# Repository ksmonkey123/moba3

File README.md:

# moba3
 3rd generation moba control

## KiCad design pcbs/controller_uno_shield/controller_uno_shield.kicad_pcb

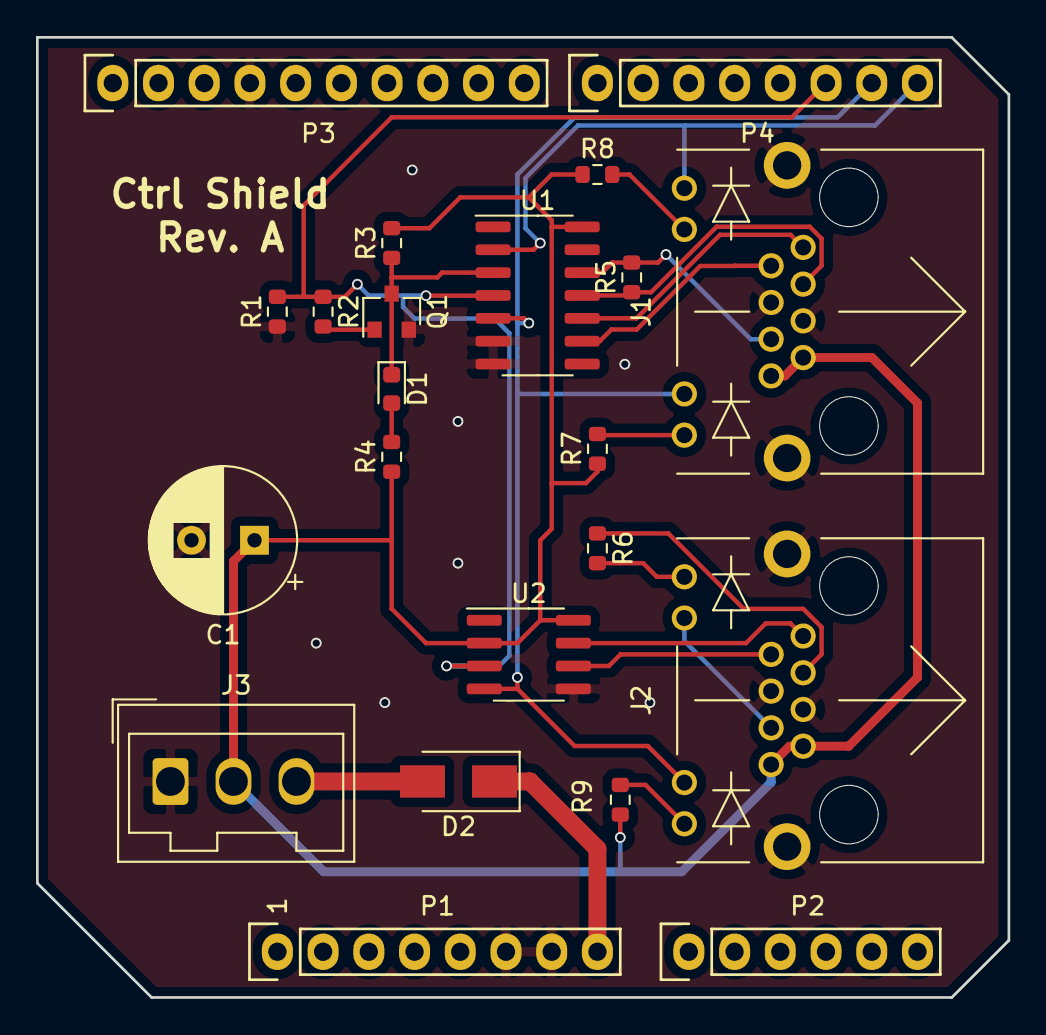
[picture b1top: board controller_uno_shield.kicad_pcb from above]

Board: 2 copper layers, 54.0 x 53.3 mm, 22 parts (0 on the bottom side), 24 nets.

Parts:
C1: CP; CP_Radial_D8.0mm_P3.50mm
D1: LED; LED_0603_1608Metric
D2: D_Schottky; D_SMA
J1, J2: RJ45_LED_Shielded; RND_RJ45_LED
J3: Screw_Terminal_01x03; Wago_734-133_1x03_P3.50mm_Vertical
P1: Power; Socket_Strip_Arduino_1x08
P2: Analog; Socket_Strip_Arduino_1x06
P3: Digital; Socket_Strip_Arduino_1x10
P4: Digital; Socket_Strip_Arduino_1x08
Q1: 2N7002; SOT-23
R1, R2, R3, R4: 10k; R_0603_1608Metric
R5: 2k; R_0603_1608Metric
R6, R7, R8, R9: 1k; R_0603_1608Metric
U1: MAX489E; SOIC-14_3.9x8.7mm_P1.27mm
U2: MAX481E; SOIC-8_3.9x4.9mm_P1.27mm

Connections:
5V: C1.1, J1.7, J1.8, J2.7, J2.8, J3.2, R3.2, R4.1, R7.1, R8.1, R9.1, U1.14, U2.2, U2.8
/0(Rx): J1.9, P4.8, U1.2
/1(Tx): J1.11, J2.11, P4.7, U1.5, U2.4
/2: P4.6, R1.2, R2.1, U1.4, U2.3
/A4(SDA): P2.5, P3.2
/A5(SCL): P2.6, P3.1
/Vin: D2.1, P1.8
/networking/~rx_en: D1.1, Q1.3, R3.1, U1.3
GND: C1.2, J1.4, J1.5, J1.SH, J2.4, J2.5, J2.SH, J3.1, P1.6, P1.7, P3.4, Q1.2, R1.1, U1.6, U1.7, U2.5
unnamed: D1.2, R4.2
unnamed: D2.2, J3.3
unnamed: J1.1, U1.10
unnamed: J1.2, U1.9
unnamed: J1.3, R5.1, U1.11
unnamed: J1.6, R5.2, U1.12
unnamed: J1.10, R8.2
unnamed: J1.12, R7.2
unnamed: J2.1, U2.7
unnamed: J2.2, U2.6
unnamed: J2.3, R6.1
unnamed: J2.9, R6.2
unnamed: J2.6, J2.10
unnamed: J2.12, R9.2
unnamed: Q1.1, R2.2

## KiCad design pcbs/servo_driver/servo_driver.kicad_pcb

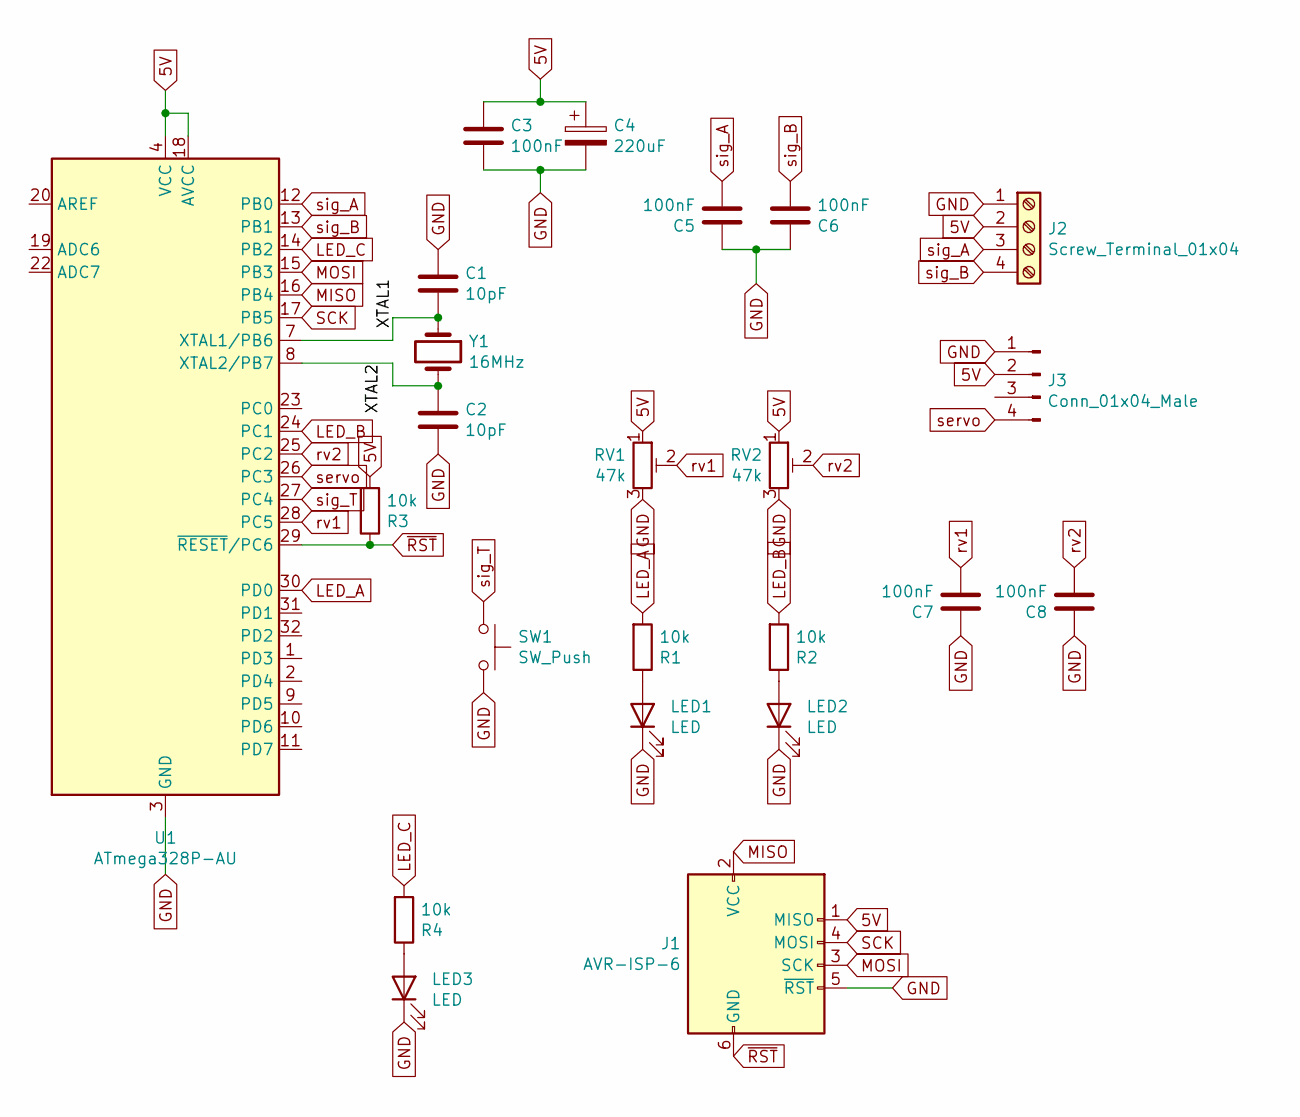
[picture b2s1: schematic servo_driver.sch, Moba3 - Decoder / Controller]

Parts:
C1, C2: 10pF; C_0603_1608Metric
C3, C5, C6, C7, C8: 100nF; C_0603_1608Metric
C4: 220uF; CP_Elec_6.3x7.7
J1: AVR-ISP-6; IDC-Header_2x03_P2.54mm_Vertical
J2: Screw_Terminal_01x04; TerminalBlock_Phoenix_MPT-0,5-4-2.54_1x04_P2.54mm_Horizontal
J3: Conn_01x04_Male; JST_PH_B4B-PH-K_1x04_P2.00mm_Vertical
LED1, LED2, LED3: LED; LED_0603_1608Metric
R1, R2, R3, R4: 10k; R_0603_1608Metric
RV1, RV2: 47k; Potentiometer_Bourns_3314J_Vertical
SW1: SW_Push; SW_PUSH_6mm_H7.3mm
U1: ATmega328P-AU; TQFP-32_7x7mm_P0.8mm
Y1: 16MHz; Crystal_HC49-4H_Vertical

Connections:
5V: C3.2, C4.1, J1.1 (MISO), J2.2, J3.2, R3.2, RV1.1, RV2.1, U1.4 (VCC), U1.6 (VCC), U1.18 (AVCC)
/XTAL1: C1.1, U1.7 (XTAL1/PB6), Y1.1
/XTAL2: C2.2, U1.8 (XTAL2/PB7), Y1.2
GND: C1.2, C2.1, C3.1, C4.2, C5.2, C6.2, C7.2, C8.2, J1.5 (~RST), J2.1, J3.1, LED1.1 (K), LED2.1 (K), LED3.1 (K), RV1.3, RV2.3, SW1.2, U1.3 (GND), U1.5 (GND), U1.21 (GND)
LED_A: R1.2, U1.30 (PD0)
LED_B: R2.2, U1.24 (PC1)
LED_C: R4.2, U1.14 (PB2)
MISO: J1.2 (VCC), U1.16 (PB4)
MOSI: J1.3 (SCK), U1.15 (PB3)
unnamed: LED1.2 (A), R1.1
unnamed: LED2.2 (A), R2.1
unnamed: LED3.2 (A), R4.1
SCK: J1.4 (MOSI), U1.17 (PB5)
rv1: C7.1, RV1.2, U1.28 (PC5)
rv2: C8.1, RV2.2, U1.25 (PC2)
servo: J3.4, U1.26 (PC3)
sig_A: C5.1, J2.3, U1.12 (PB0)
sig_B: C6.1, J2.4, U1.13 (PB1)
sig_T: SW1.1, U1.27 (PC4)
~RST: J1.6 (GND), R3.1, U1.29 (~RESET~/PC6)

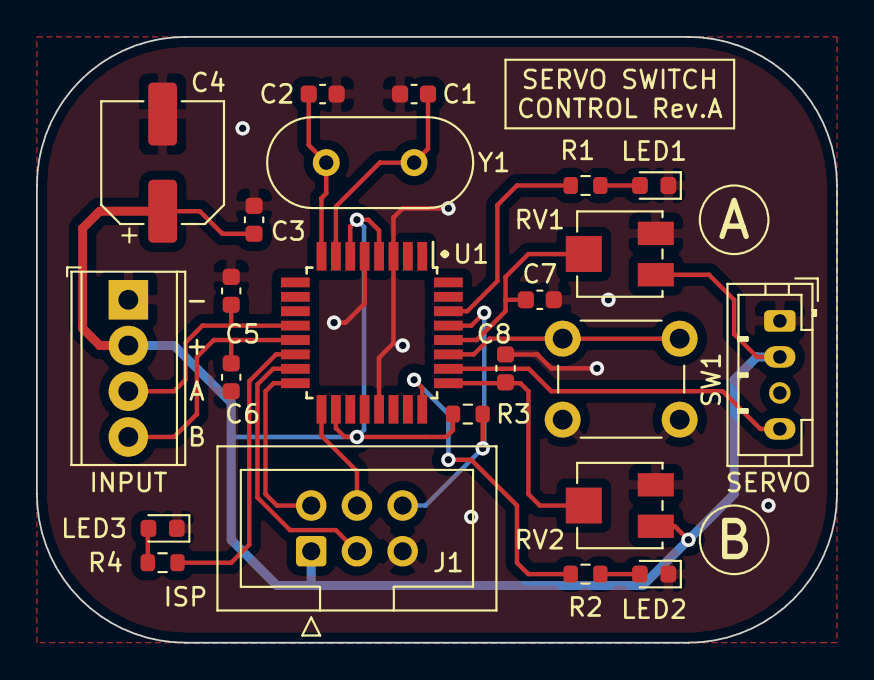
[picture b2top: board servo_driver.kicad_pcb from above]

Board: 2 copper layers, 44.4 x 33.7 mm, 23 parts (0 on the bottom side), 20 nets.

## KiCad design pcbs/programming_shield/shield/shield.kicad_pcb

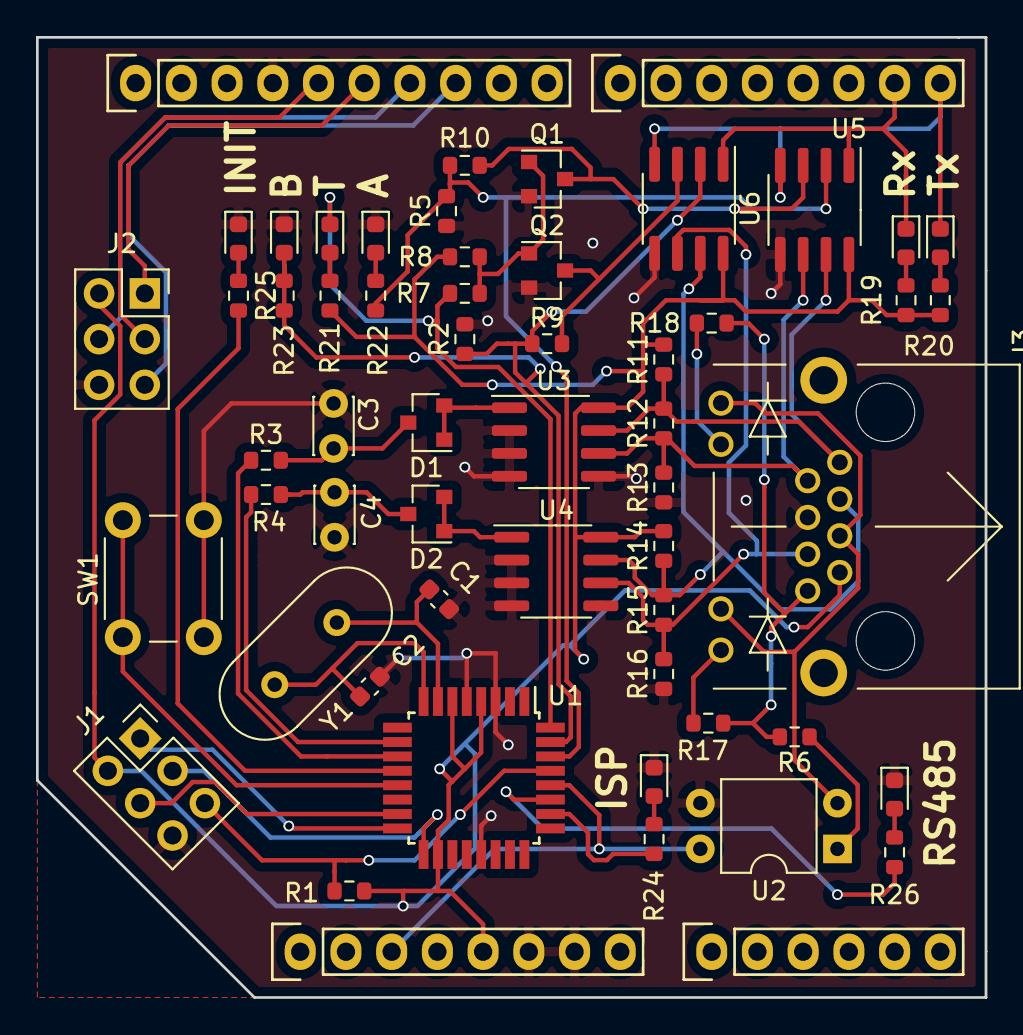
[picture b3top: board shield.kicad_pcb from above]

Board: 2 copper layers, 52.7 x 53.3 mm, 57 parts (0 on the bottom side), 48 nets.

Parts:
C1, C2: 10pF; C_0603_1608Metric
C3, C4: 100nF; C_Disc_D3.0mm_W2.0mm_P2.50mm
D1, D2: BAT54CW; SOT-23
D3, D4, D5, D6, D7, D8, D9, D10: LED; LED_0603_1608Metric
J1, J2: AVR-ISP-6; PinSocket_2x03_P2.54mm_Vertical
J3: RJ45_LED; RND_RJ45_LED
P1: Power; Socket_Strip_Arduino_1x08
P2: Analog; Socket_Strip_Arduino_1x06
P3: Digital; Socket_Strip_Arduino_1x10
P4: Digital; Socket_Strip_Arduino_1x08
Q1, Q2: 2N7002; SOT-23
R1, R2, R5, R7, R8, R9, R10, R12, R15: 10k; R_0603_1608Metric
R3, R4, R6, R11, R13, R14, R16: 1k; R_0603_1608Metric
R17, R18, R19, R20, R21, R22, R23, R24, R25, R26: R; R_0603_1608Metric
SW1: SW_Push; SW_PUSH_6mm
U1: ATmega328P-AU; TQFP-32_7x7mm_P0.8mm
U2: EL817; DIP-4_W7.62mm
U3, U4, U5, U6: ST485EBDR; SOIC-8_3.9x4.9mm_P1.27mm
Y1: 16MHz; Crystal_HC49-4H_Vertical

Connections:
+5V: J1.2, J2.2, J3.7, P1.5, R1.2, R8.1, R11.2, R14.2, R19.2, R20.2, R21.2, U1.4, U1.6, U1.18, U3.8, U4.8, U5.8, U6.8
/0(Rx): D4.1, P4.8, U5.4, U6.4
/1(Tx): D3.1, P4.7, U5.1, U6.1
/10(**/SS): J2.5, P3.8
/11(**/MOSI): J2.4, P3.7
/12(MISO): J2.1, P3.6
/13(SCK): J2.3, P3.5
/CopMISO: J1.1, U1.16
/CopMOSI: J1.4, U1.15
/CopRST: J1.5, R1.1, U1.29
/CopSCK: J1.3, U1.17
/Reset: P1.3, U1.28, U2.4
/driveA: R5.2, R10.2, R22.2, U1.30, U5.2
/driveB: R2.1, R9.1, R23.2, U1.31, U6.2
/driveInhibit: D5.1, R7.1, U1.32
/sense+: J3.8, R6.2, R17.1, R18.1
/sense-: J3.5, J3.9, J3.11, U2.2
GND: C1.1, C2.2, C3.2, C4.2, D6.1, D7.1, D8.1, D9.1, D10.1, J1.6, J2.6, J3.4, P1.6, P1.7, P3.4, Q1.2, Q2.2, R2.2, R5.1, R13.1, R16.1, SW1.2, U1.3, U1.5, U1.21, U2.3, U3.2, U3.3, U3.4, U3.5, U4.2, U4.3, U4.4, U4.5, U5.5, U6.5
unnamed: C1.2, U1.7, Y1.1
unnamed: C2.1, U1.8, Y1.2
unnamed: C3.1, D1.3, R3.2
unnamed: C4.1, D2.3, R4.2
unnamed: D1.1, D1.2, U3.1
unnamed: D2.1, D2.2, U4.1
unnamed: D3.2, R19.1
unnamed: D4.2, R20.1
unnamed: D5.2, R21.1
unnamed: D6.2, R22.1
unnamed: D7.2, R23.1
unnamed: D8.2, R24.1
unnamed: D9.2, R25.1
unnamed: D10.2, R26.1
unnamed: J3.1, R11.1, R12.2, U3.7, U5.7
unnamed: J3.2, R12.1, R13.2, U3.6, U5.6
unnamed: J3.3, R14.1, R15.2, U4.7, U6.7
unnamed: J3.6, R15.1, R16.2, U4.6, U6.6
unnamed: J3.10, R18.2
unnamed: J3.12, R17.2
unnamed: Q1.1, Q2.1, R7.2, R8.2
unnamed: Q1.3, R10.1, U5.3
unnamed: Q2.3, R9.2, U6.3
unnamed: R3.1, U1.11
unnamed: R4.1, U1.10
unnamed: R6.1, U2.1
unnamed: R24.2, U1.26
unnamed: R25.2, U1.12
unnamed: R26.2, U1.27
unnamed: SW1.1, U1.13

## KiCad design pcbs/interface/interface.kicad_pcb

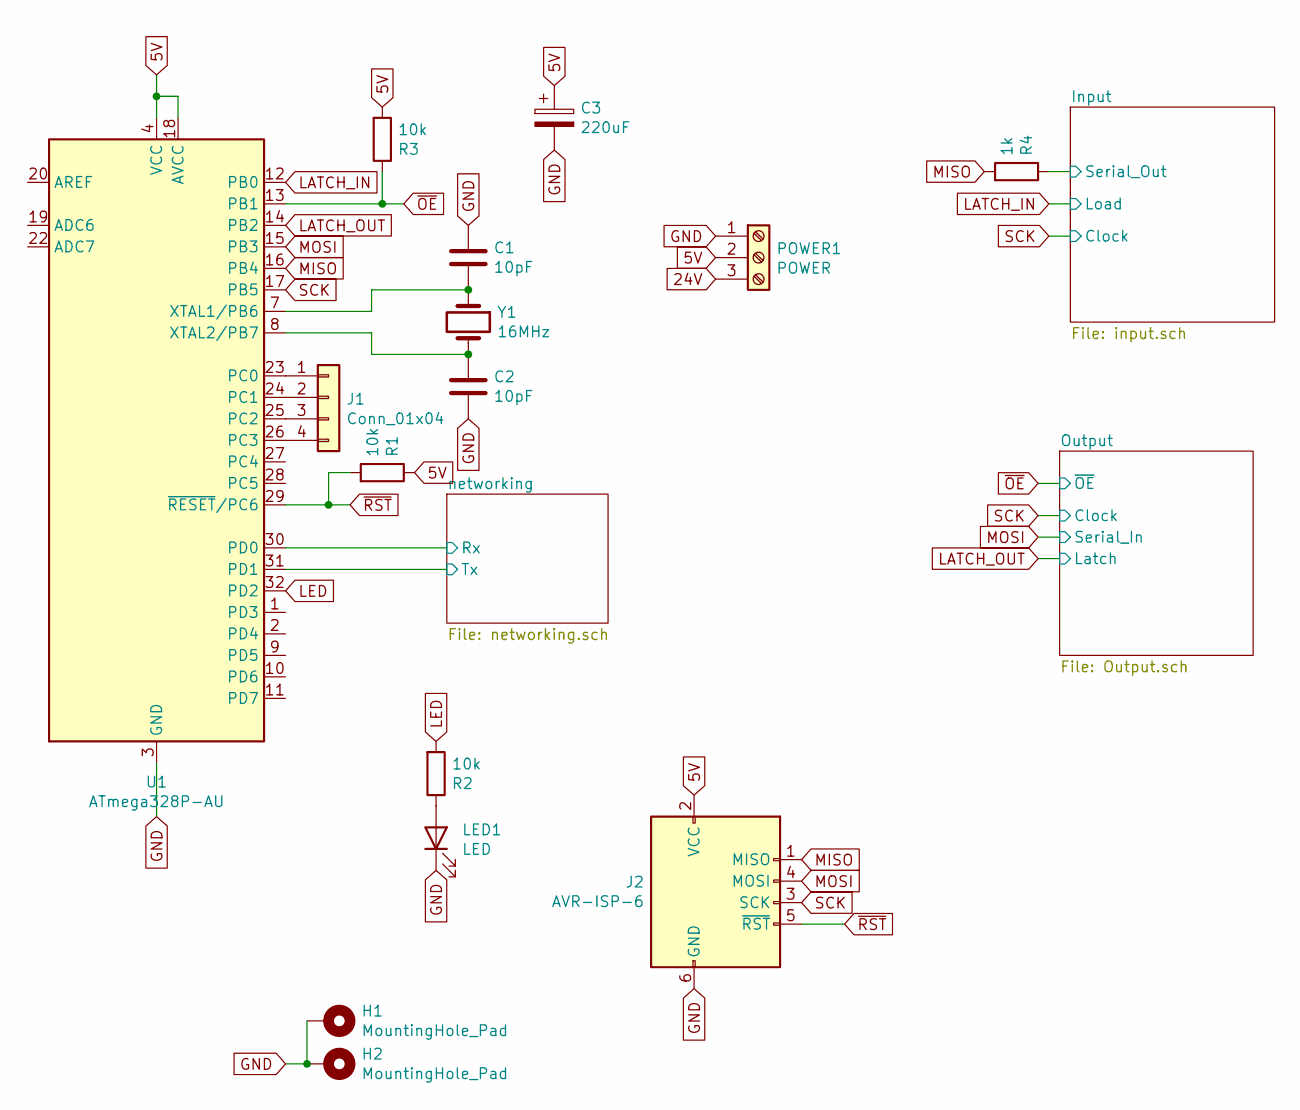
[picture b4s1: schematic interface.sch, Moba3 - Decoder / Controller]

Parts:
C1, C2: 10pF; C_0603_1608Metric
C3: 220uF; CP_Radial_D8.0mm_P3.50mm
H1, H2: MountingHole_Pad; MountingHole_3.5mm_Pad_Via
J1: Conn_01x04; PinHeader_1x04_P2.54mm_Vertical
J2: AVR-ISP-6; PinSocket_2x03_P2.54mm_Vertical
LED1: LED; LED_0603_1608Metric
POWER1: POWER; Wago_734-133_1x03_P3.50mm_Vertical
R1, R2, R3: 10k; R_0603_1608Metric
R4: 1k; R_0603_1608Metric
U1: ATmega328P-AU; TQFP-32_7x7mm_P0.8mm
Y1: 16MHz; Crystal_HC49-4H_Vertical

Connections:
5V: C3.1, J2.2 (VCC), POWER1.2, R1.1, R3.2, U1.4 (VCC), U1.6 (VCC), U1.18 (AVCC); also elsewhere on the board
/Input/Serial_Out: R4.1; also elsewhere on the board
/networking/Rx: U1.30 (PD0); also elsewhere on the board
/networking/Tx: U1.31 (PD1); also elsewhere on the board
GND: C1.2, C2.1, C3.2, H1.1, H2.1, J2.6 (GND), LED1.1 (K), POWER1.1, U1.3 (GND), U1.5 (GND), U1.21 (GND); also elsewhere on the board
LATCH_IN: U1.12 (PB0); also elsewhere on the board
LATCH_OUT: U1.14 (PB2); also elsewhere on the board
LED: R2.2, U1.32 (PD2)
MISO: J2.1 (MISO), R4.2, U1.16 (PB4)
MOSI: J2.4 (MOSI), U1.15 (PB3); also elsewhere on the board
unnamed: C1.1, U1.7 (XTAL1/PB6), Y1.1
unnamed: C2.2, U1.8 (XTAL2/PB7), Y1.2
unnamed: J1.1, U1.23 (PC0)
unnamed: J1.2, U1.24 (PC1)
unnamed: J1.3, U1.25 (PC2)
unnamed: J1.4, U1.26 (PC3)
unnamed: LED1.2 (A), R2.1
SCK: J2.3 (SCK), U1.17 (PB5); also elsewhere on the board
~OE: R3.1, U1.13 (PB1); also elsewhere on the board
~RST: J2.5 (~RST), R1.2, U1.29 (~RESET~/PC6)

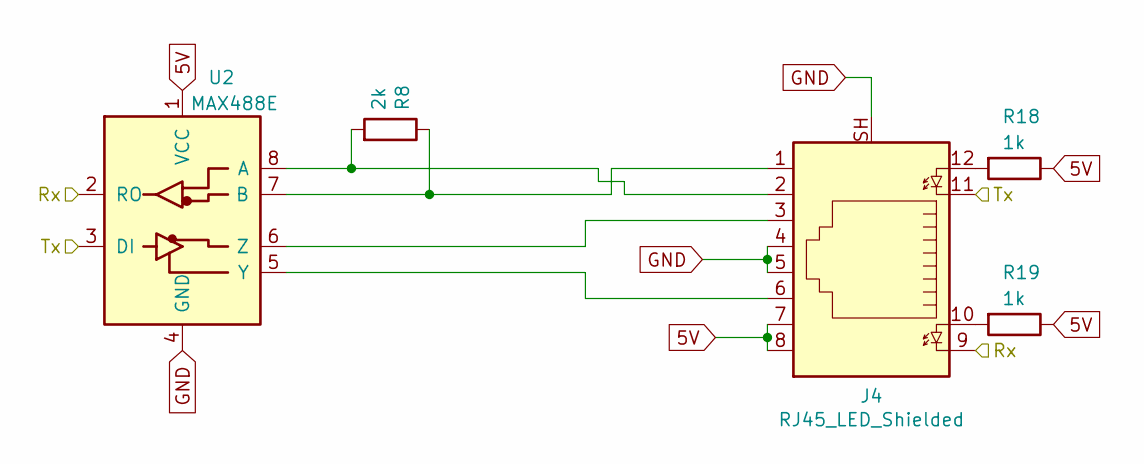
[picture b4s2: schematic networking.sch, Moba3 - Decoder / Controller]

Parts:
J4: RJ45_LED_Shielded; RND_RJ45_LED
R8: 2k; R_0603_1608Metric
R18, R19: 1k; R_0603_1608Metric
U2: MAX488E; SOIC-8_3.9x4.9mm_P1.27mm

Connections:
5V: J4.7, J4.8, R18.1, R19.1, U2.1 (VCC); also elsewhere on the board
/networking/Rx: J4.9, U2.2 (RO); also elsewhere on the board
/networking/Tx: J4.11, U2.3 (DI); also elsewhere on the board
GND: J4.4, J4.5, J4.SH, U2.4 (GND); also elsewhere on the board
unnamed: J4.1, R8.1, U2.7 (B)
unnamed: J4.2, R8.2, U2.8 (A)
unnamed: J4.3, U2.6 (Z)
unnamed: J4.6, U2.5 (Y)
unnamed: J4.10, R19.2
unnamed: J4.12, R18.2

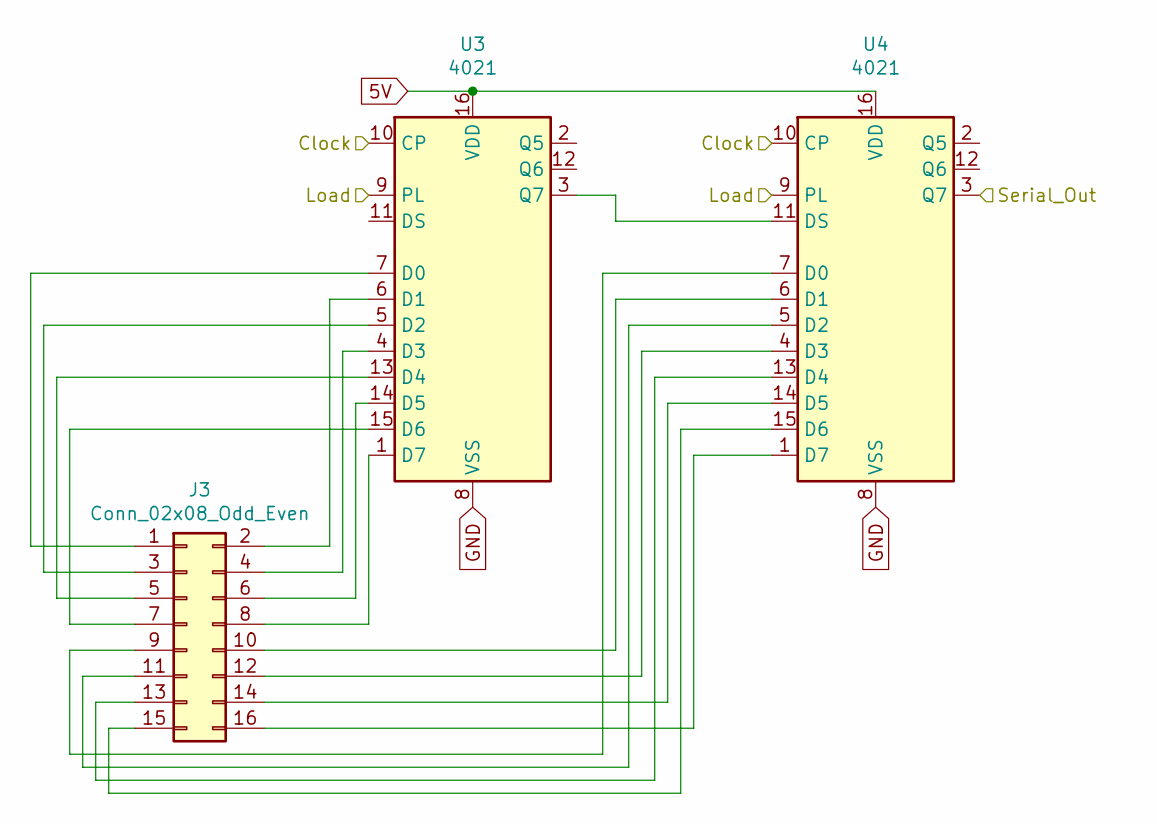
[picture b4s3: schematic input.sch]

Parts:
J3: Conn_02x08_Odd_Even; PinHeader_2x08_P2.54mm_Vertical
U3, U4: 4021; SOIC-16_3.9x9.9mm_P1.27mm

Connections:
5V: U3.16 (VDD), U4.16 (VDD); also elsewhere on the board
/Input/Serial_Out: U4.3 (Q7); also elsewhere on the board
GND: U3.8 (VSS), U4.8 (VSS); also elsewhere on the board
LATCH_IN: U3.9 (PL), U4.9 (PL); also elsewhere on the board
unnamed: J3.1, U3.7 (D0)
unnamed: J3.2, U3.6 (D1)
unnamed: J3.3, U3.5 (D2)
unnamed: J3.4, U3.4 (D3)
unnamed: J3.5, U3.13 (D4)
unnamed: J3.6, U3.14 (D5)
unnamed: J3.7, U3.15 (D6)
unnamed: J3.8, U3.1 (D7)
unnamed: J3.9, U4.7 (D0)
unnamed: J3.10, U4.6 (D1)
unnamed: J3.11, U4.5 (D2)
unnamed: J3.12, U4.4 (D3)
unnamed: J3.13, U4.13 (D4)
unnamed: J3.14, U4.14 (D5)
unnamed: J3.15, U4.15 (D6)
unnamed: J3.16, U4.1 (D7)
unnamed: U3.3 (Q7), U4.11 (DS)
SCK: U3.10 (CP), U4.10 (CP); also elsewhere on the board

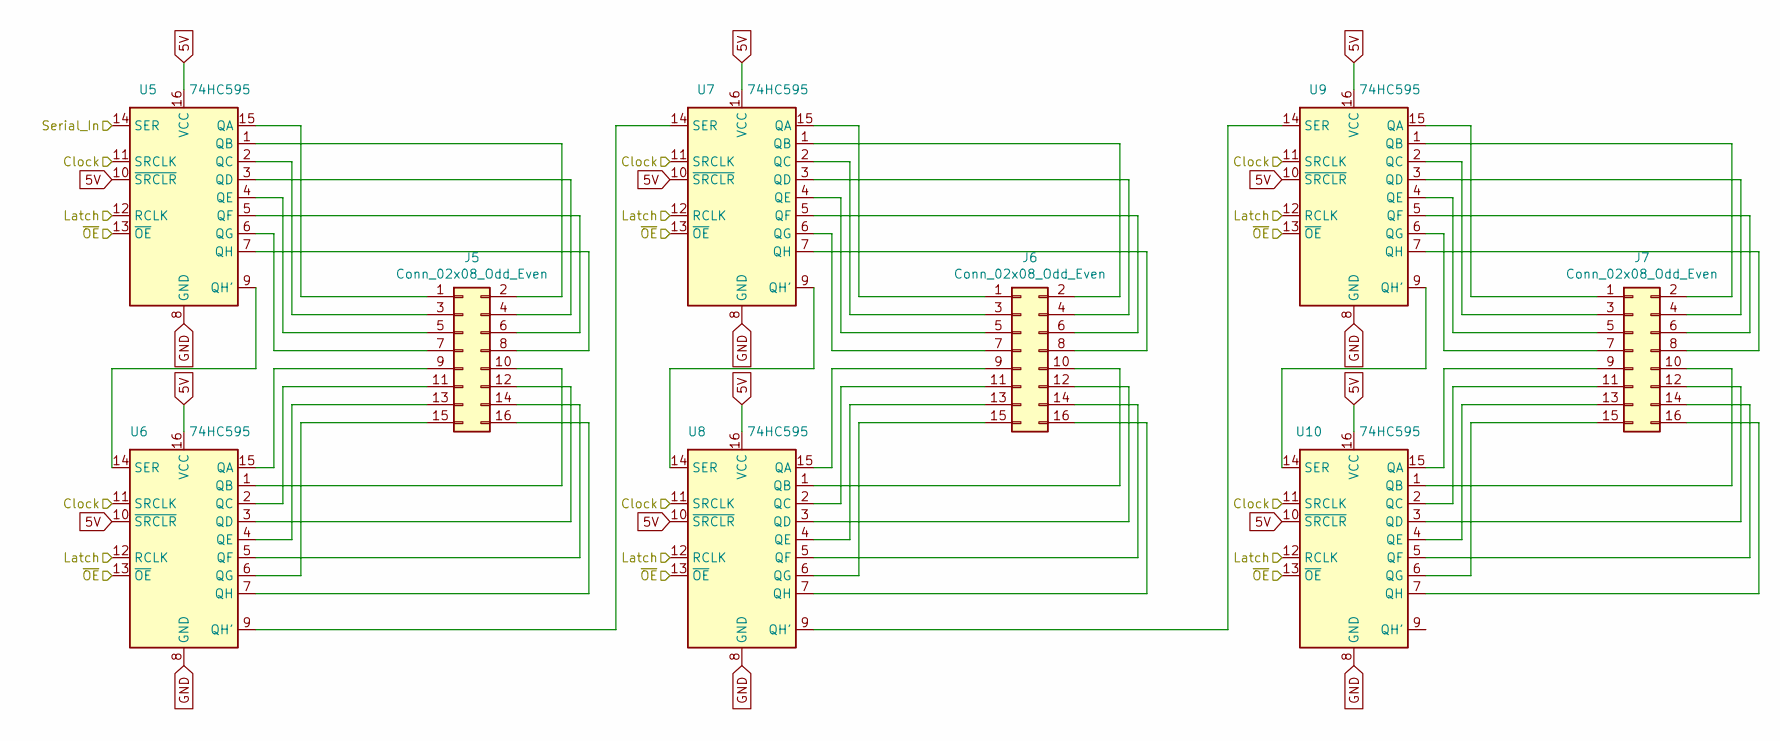
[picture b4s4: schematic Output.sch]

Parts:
J5, J6, J7: Conn_02x08_Odd_Even; PinHeader_2x08_P2.54mm_Vertical
U5, U6, U7, U8, U9, U10: 74HC595; SOIC-16_3.9x9.9mm_P1.27mm

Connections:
5V: U5.10 (~SRCLR), U5.16 (VCC), U6.10 (~SRCLR), U6.16 (VCC), U7.10 (~SRCLR), U7.16 (VCC), U8.10 (~SRCLR), U8.16 (VCC), U9.10 (~SRCLR), U9.16 (VCC), U10.10 (~SRCLR), U10.16 (VCC); also elsewhere on the board
GND: U5.8 (GND), U6.8 (GND), U7.8 (GND), U8.8 (GND), U9.8 (GND), U10.8 (GND); also elsewhere on the board
LATCH_OUT: U5.12 (RCLK), U6.12 (RCLK), U7.12 (RCLK), U8.12 (RCLK), U9.12 (RCLK), U10.12 (RCLK); also elsewhere on the board
MOSI: U5.14 (SER); also elsewhere on the board
unnamed: J5.1, U5.15 (QA)
unnamed: J5.2, U5.1 (QB)
unnamed: J5.3, U5.2 (QC)
unnamed: J5.4, U5.3 (QD)
unnamed: J5.5, U5.4 (QE)
unnamed: J5.6, U5.5 (QF)
unnamed: J5.7, U5.6 (QG)
unnamed: J5.8, U5.7 (QH)
unnamed: J5.9, U6.15 (QA)
unnamed: J5.10, U6.1 (QB)
unnamed: J5.11, U6.2 (QC)
unnamed: J5.12, U6.3 (QD)
unnamed: J5.13, U6.4 (QE)
unnamed: J5.14, U6.5 (QF)
unnamed: J5.15, U6.6 (QG)
unnamed: J5.16, U6.7 (QH)
unnamed: J6.1, U7.15 (QA)
unnamed: J6.2, U7.1 (QB)
unnamed: J6.3, U7.2 (QC)
unnamed: J6.4, U7.3 (QD)
unnamed: J6.5, U7.4 (QE)
unnamed: J6.6, U7.5 (QF)
unnamed: J6.7, U7.6 (QG)
unnamed: J6.8, U7.7 (QH)
unnamed: J6.9, U8.15 (QA)
unnamed: J6.10, U8.1 (QB)
unnamed: J6.11, U8.2 (QC)
unnamed: J6.12, U8.3 (QD)
unnamed: J6.13, U8.4 (QE)
unnamed: J6.14, U8.5 (QF)
unnamed: J6.15, U8.6 (QG)
unnamed: J6.16, U8.7 (QH)
unnamed: J7.1, U9.15 (QA)
unnamed: J7.2, U9.1 (QB)
unnamed: J7.3, U9.2 (QC)
unnamed: J7.4, U9.3 (QD)
unnamed: J7.5, U9.4 (QE)
unnamed: J7.6, U9.5 (QF)
unnamed: J7.7, U9.6 (QG)
unnamed: J7.8, U9.7 (QH)
unnamed: J7.9, U10.15 (QA)
unnamed: J7.10, U10.1 (QB)
unnamed: J7.11, U10.2 (QC)
unnamed: J7.12, U10.3 (QD)
unnamed: J7.13, U10.4 (QE)
unnamed: J7.14, U10.5 (QF)
unnamed: J7.15, U10.6 (QG)
unnamed: J7.16, U10.7 (QH)
unnamed: U5.9 (QH'), U6.14 (SER)
unnamed: U6.9 (QH'), U7.14 (SER)
unnamed: U7.9 (QH'), U8.14 (SER)
unnamed: U8.9 (QH'), U9.14 (SER)
unnamed: U9.9 (QH'), U10.14 (SER)
SCK: U5.11 (SRCLK), U6.11 (SRCLK), U7.11 (SRCLK), U8.11 (SRCLK), U9.11 (SRCLK), U10.11 (SRCLK); also elsewhere on the board
~OE: U5.13 (~OE), U6.13 (~OE), U7.13 (~OE), U8.13 (~OE), U9.13 (~OE), U10.13 (~OE); also elsewhere on the board

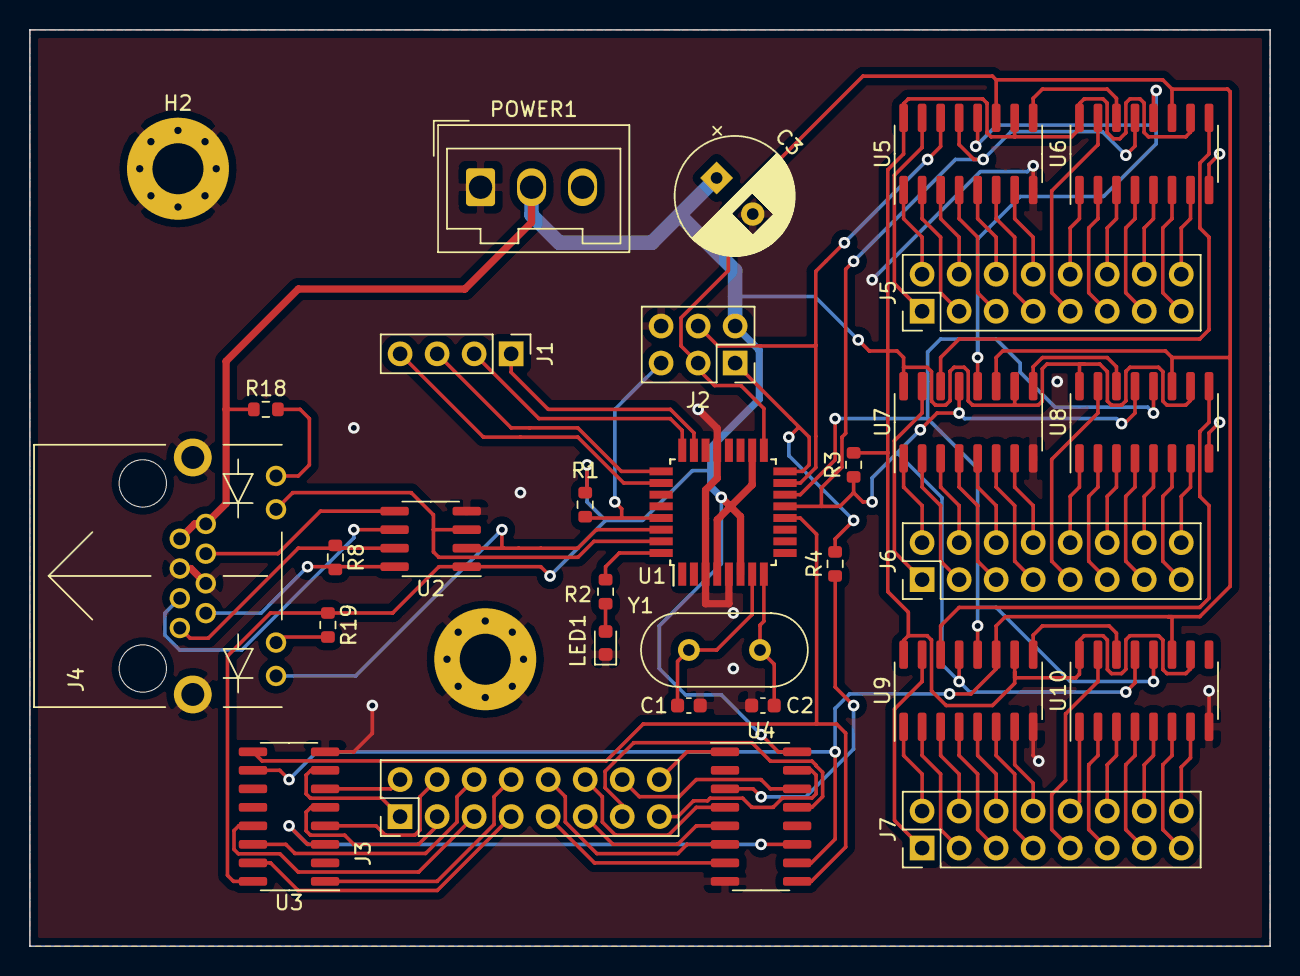
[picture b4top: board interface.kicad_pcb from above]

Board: 2 copper layers, 85.1 x 62.9 mm, 32 parts (0 on the bottom side), 96 nets.

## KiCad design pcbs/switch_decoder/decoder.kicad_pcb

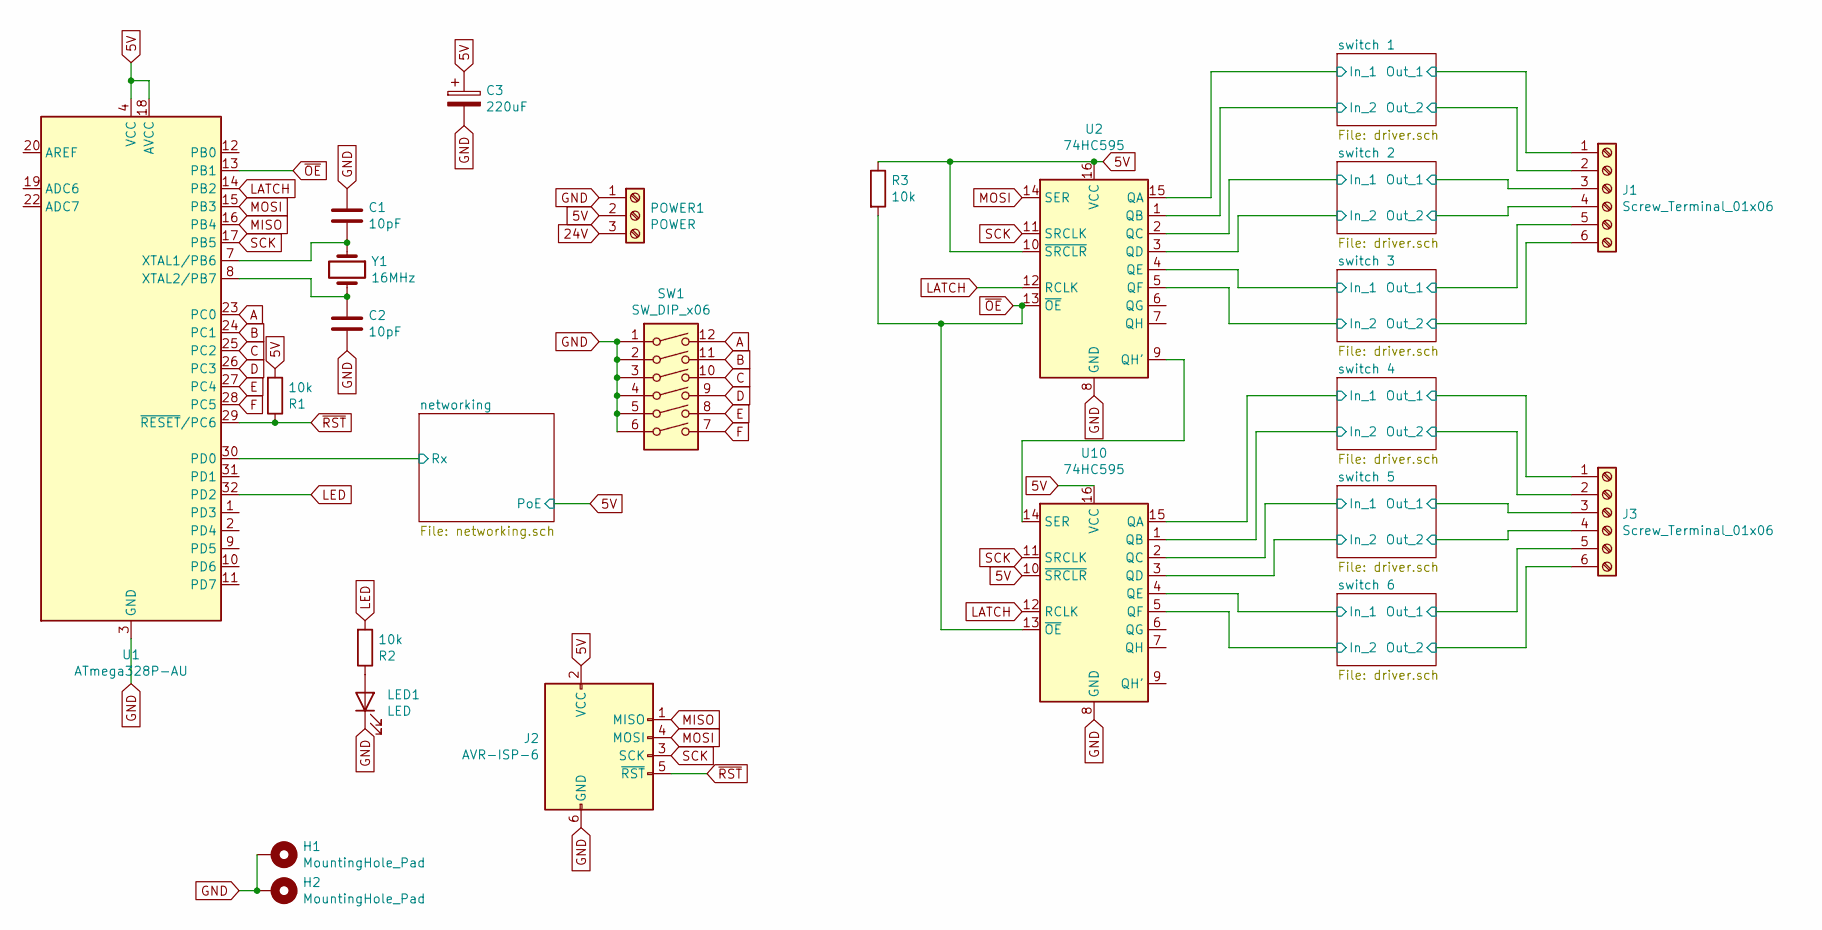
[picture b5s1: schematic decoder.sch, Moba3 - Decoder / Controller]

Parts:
C1, C2: 10pF; C_0603_1608Metric
C3: 220uF; CP_Radial_D8.0mm_P3.50mm
H1, H2: MountingHole_Pad; MountingHole_3.5mm_Pad_Via
J1, J3: Screw_Terminal_01x06; Wago_734-136_1x06_P3.50mm_Vertical
J2: AVR-ISP-6; PinSocket_2x03_P2.54mm_Vertical
LED1: LED; LED_0603_1608Metric
POWER1: POWER; Wago_734-133_1x03_P3.50mm_Vertical
R1, R2, R3: 10k; R_0603_1608Metric
SW1: SW_DIP_x06; SW_DIP_SPSTx06_Slide_KingTek_DSHP06TJ_W5.25mm_P1.27mm_JPin
U1: ATmega328P-AU; TQFP-32_7x7mm_P0.8mm
U2, U10: 74HC595; SOIC-16_3.9x9.9mm_P1.27mm
Y1: 16MHz; Crystal_HC49-4H_Vertical

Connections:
5V: C3.1, J2.2 (VCC), POWER1.2, R1.2, R3.1, U1.4 (VCC), U1.6 (VCC), U1.18 (AVCC), U2.10 (~SRCLR), U2.16 (VCC), U10.10 (~SRCLR), U10.16 (VCC); also elsewhere on the board
24V: POWER1.3; also elsewhere on the board
/networking/Rx: U1.30 (PD0); also elsewhere on the board
/switch 1/Out_1: J1.1; also elsewhere on the board
/switch 1/Out_2: J1.2; also elsewhere on the board
/switch 2/In_1: U2.2 (QC); also elsewhere on the board
/switch 2/Out_1: J1.3; also elsewhere on the board
/switch 2/Out_2: J1.4; also elsewhere on the board
/switch 3/In_1: U2.4 (QE); also elsewhere on the board
/switch 3/In_2: U2.5 (QF); also elsewhere on the board
/switch 3/Out_1: J1.5; also elsewhere on the board
/switch 3/Out_2: J1.6; also elsewhere on the board
/switch 4/In_1: U10.15 (QA); also elsewhere on the board
/switch 4/Out_1: J3.1; also elsewhere on the board
/switch 4/Out_2: J3.2; also elsewhere on the board
/switch 5/In_1: U10.2 (QC); also elsewhere on the board
/switch 5/In_2: U10.3 (QD); also elsewhere on the board
/switch 5/Out_1: J3.3; also elsewhere on the board
/switch 5/Out_2: J3.4; also elsewhere on the board
/switch 6/In_1: U10.4 (QE); also elsewhere on the board
/switch 6/In_2: U10.5 (QF); also elsewhere on the board
/switch 6/Out_1: J3.5; also elsewhere on the board
/switch 6/Out_2: J3.6; also elsewhere on the board
A: SW1.12, U1.23 (PC0)
B: SW1.11, U1.24 (PC1)
C: SW1.10, U1.25 (PC2)
D: SW1.9, U1.26 (PC3)
E: SW1.8, U1.27 (PC4)
F: SW1.7, U1.28 (PC5)
GND: C1.2, C2.1, C3.2, H1.1, H2.1, J2.6 (GND), LED1.1 (K), POWER1.1, SW1.1, SW1.2, SW1.3, SW1.4, SW1.5, SW1.6, U1.3 (GND), U1.5 (GND), U1.21 (GND), U2.8 (GND), U10.8 (GND); also elsewhere on the board
LATCH: U1.14 (PB2), U2.12 (RCLK), U10.12 (RCLK)
LED: R2.2, U1.32 (PD2)
MISO: J2.1 (MISO), U1.16 (PB4)
MOSI: J2.4 (MOSI), U1.15 (PB3), U2.14 (SER)
unnamed: C1.1, U1.7 (XTAL1/PB6), Y1.1
unnamed: C2.2, U1.8 (XTAL2/PB7), Y1.2
unnamed: LED1.2 (A), R2.1
unnamed: U2.9 (QH'), U10.14 (SER)
SCK: J2.3 (SCK), U1.17 (PB5), U2.11 (SRCLK), U10.11 (SRCLK)
~OE: R3.2, U1.13 (PB1), U2.13 (~OE), U10.13 (~OE)
~RST: J2.5 (~RST), R1.1, U1.29 (~RESET~/PC6)

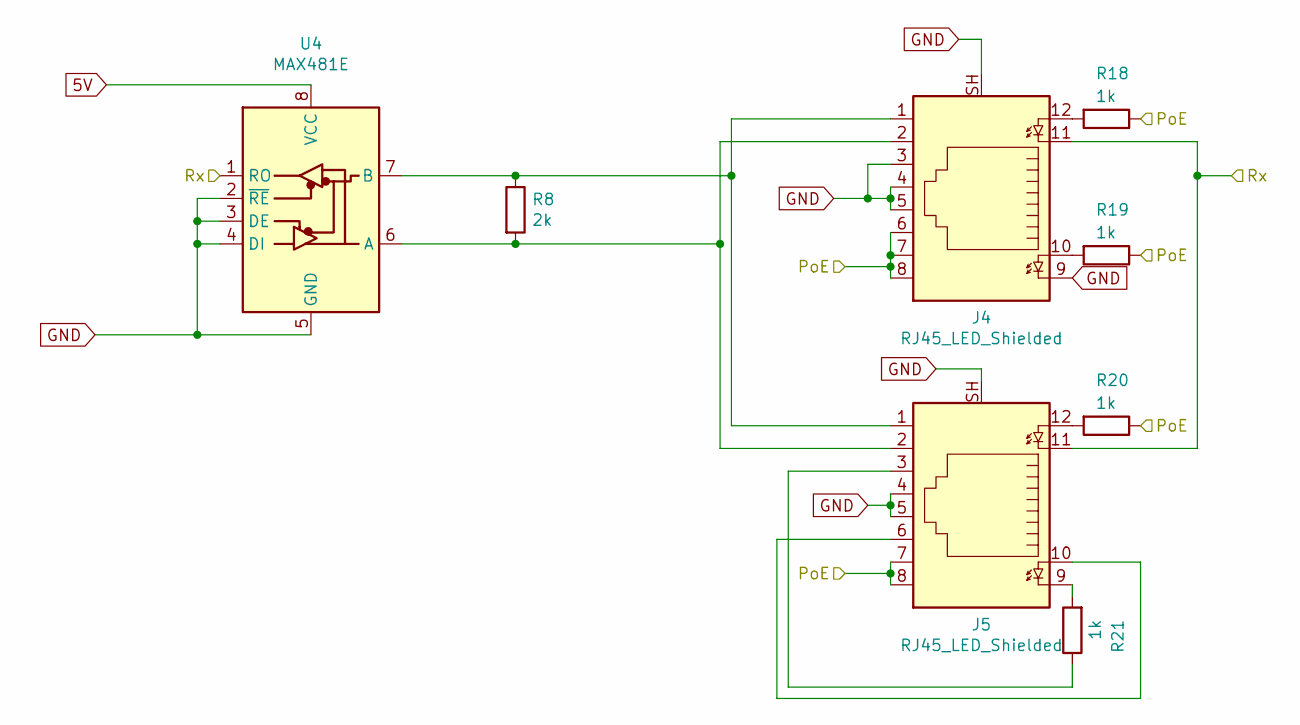
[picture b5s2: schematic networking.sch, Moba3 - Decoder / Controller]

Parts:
J4, J5: RJ45_LED_Shielded; RND_RJ45_LED
R8: 2k; R_0603_1608Metric
R18, R19, R20, R21: 1k; R_0603_1608Metric
U4: MAX481E; SOIC-8_3.9x4.9mm_P1.27mm

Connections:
5V: J4.6, J4.7, J4.8, J5.7, J5.8, R18.1, R19.1, R20.1, U4.8 (VCC); also elsewhere on the board
/networking/Rx: J4.11, J5.11, U4.1 (RO); also elsewhere on the board
GND: J4.3, J4.4, J4.5, J4.9, J4.SH, J5.4, J5.5, J5.SH, U4.2 (~RE), U4.3 (DE), U4.4 (DI), U4.5 (GND); also elsewhere on the board
unnamed: J4.1, J5.1, R8.1, U4.7 (B)
unnamed: J4.2, J5.2, R8.2, U4.6 (A)
unnamed: J4.10, R19.2
unnamed: J4.12, R18.2
unnamed: J5.3, R21.1
unnamed: J5.9, R21.2
unnamed: J5.6, J5.10
unnamed: J5.12, R20.2
